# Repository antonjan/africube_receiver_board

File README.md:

This Repository has the Africube SDR Recever Boards V1.0<br>
Project is compleet but boards has not been build yet 3 Feb 2021
<br>

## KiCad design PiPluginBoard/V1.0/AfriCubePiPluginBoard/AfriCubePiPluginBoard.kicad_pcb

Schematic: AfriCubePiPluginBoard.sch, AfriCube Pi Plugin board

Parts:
BT1: Battery_Cell_3V; BatteryHolder_Keystone_3000_1x12mm
C1, C6, C7: 47uF; R_1210_3225Metric_Pad1.42x2.65mm_HandSolder
C2, C4, C11, C13, C14: 100nF; R_0805_2012Metric_Pad1.15x1.40mm_HandSolder
C3, C10, C12: 10uF; R_0805_2012Metric_Pad1.15x1.40mm_HandSolder
C5: 4.7uF; R_0805_2012Metric_Pad1.15x1.40mm_HandSolder
C9: 1uF; R_0805_2012Metric_Pad1.15x1.40mm_HandSolder
D1, D2: LED; R_0805_2012Metric_Pad1.15x1.40mm_HandSolder
D3, D4: BAV99; SOT-23
J1: USB_A; PinHeader_1x05_P1.00mm_Vertical
J2: SD_Card; microSD_HC_Hirose_DM3D-SF
J3: USB_B_Mini; USB_Mini-B_Lumberg_2486_01_Horizontal
J4: SODIMM-200; Conn_TE-DDR2-SODIMM-0.6-200P-doublesided
J7: Conn_01x04_Male; PinSocket_1x04_P2.54mm_Vertical
JP1: Jumper_Boot_Select; PinSocket_1x03_P2.54mm_Vertical
JP2: WDT_S0; SolderJumper-3_P1.3mm_Open_RoundedPad1.0x1.5mm
JP3: WDT_S1; SolderJumper-3_P1.3mm_Open_RoundedPad1.0x1.5mm
JP4: WDT_S2; SolderJumper-3_P1.3mm_Open_RoundedPad1.0x1.5mm
Q1, Q2, Q3: BSS138; SOT-23
R1, R3, R6: 47K; R_0805_2012Metric_Pad1.15x1.40mm_HandSolder
R2, R7: 470R; R_0805_2012Metric_Pad1.15x1.40mm_HandSolder
R4, R5, R8, R9, R10, R11, R14, R15, R16: 100K; R_0805_2012Metric_Pad1.15x1.40mm_HandSolder
R12, R13: 4K7; R_0805_2012Metric_Pad1.15x1.40mm_HandSolder
R17, R19: 270R; R_0805_2012Metric_Pad1.15x1.40mm_HandSolder
R18, R20: 150R; R_0805_2012Metric_Pad1.15x1.40mm_HandSolder
U1: FSUSB42MUX; MSOP-10_3x3mm_P0.5mm
U2: TLV70218_SOT23-5; SOT-23-5
U3: MAX6373; SOT-23-8
U4: DS3231M; SOIC-16W_7.5x10.3mm_P1.27mm

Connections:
+1V8: C3.1, J4.183, J4.184, J4.185, J4.186, R4.1, U2.5
+3V3: C4.1, C5.2, C7.2, C9.1, C14.1, D3.3, D4.3, J2.4, J4.39, J4.40, J4.41, J4.42, J4.191, J4.192, J4.193, J4.194, JP2.1, JP3.1, JP4.1, R1.2, R2.1, R7.1, R12.1, R13.1, R14.1, R15.1, R16.1, U1.1 (Vcc), U3.8, U4.2; also elsewhere on the board
+5V: C1.1, C6.1, J1.1, J4.197, J4.198, J4.199, R5.2, U2.1; also elsewhere on the board
+5V_USB: J3.1, JP1.1, Q3.1, R6.1; also elsewhere on the board
/Audio_L: J4.70, R17.2
/Audio_R: J4.84, R11.1, R19.2
/EMMC_DISABLE_N: J4.2, Q1.3
/EMMC_EN_N_1V8: J4.90, Q2.1, R4.2
/RTC_Int: J4.76, R15.2, U4.3
/RTC_Rst: J4.78, R16.2, U4.4
/USB_DM: J4.167, U1.4 (D-)
/USB_DP: J4.165, U1.3 (D+)
ANT_RELEASE: J4.81; also elsewhere on the board
BATT_OFF: J4.63; also elsewhere on the board
CHG_INH: J4.75; also elsewhere on the board
EPS_EOC: J4.57; also elsewhere on the board
EPS_SPI_CLK: J4.35; also elsewhere on the board
EPS_SPI_CS: J4.27; also elsewhere on the board
EPS_SPI_MISO: J4.29; also elsewhere on the board
EPS_SPI_MOSI: J4.33; also elsewhere on the board
GPIO4: J4.15; also elsewhere on the board
GPIO5: J4.17; also elsewhere on the board
GPIO6: J4.21; also elsewhere on the board
GPIO7: J4.23; also elsewhere on the board
GPIO12: J4.45; also elsewhere on the board
GPIO13: J4.47; also elsewhere on the board
GPIO14: J4.51; also elsewhere on the board
GPIO15: J4.53; also elsewhere on the board
GPIO17: J4.59; also elsewhere on the board
GPIO19: J4.65; also elsewhere on the board
GPIO21: J4.71; also elsewhere on the board
GPIO23: J4.77; also elsewhere on the board
GPIO25: J4.83; also elsewhere on the board
GPIO26: J4.87; also elsewhere on the board
GPIO27: J4.89; also elsewhere on the board
unnamed: BT1.1, U4.14
unnamed: C2.1, R5.1, U2.3
unnamed: C10.1, D3.1, D3.2, J7.1
unnamed: C10.2, C11.1, R17.1, R18.2
unnamed: C12.1, D4.1, D4.2, J7.3
unnamed: C12.2, C13.1, R19.1, R20.2
unnamed: D1.1, Q1.2, Q2.3
unnamed: D1.2, R2.2
unnamed: D2.2, R7.2
unnamed: J1.2, U1.8 (HSD2-)
unnamed: J1.3, U1.9 (HSD2+)
unnamed: J2.1, J4.24
unnamed: J2.2, J4.12
unnamed: J2.5, J4.10
unnamed: J2.7, J4.16
unnamed: J2.8, J4.18
unnamed: J2.9, J4.22
unnamed: J3.2, U1.6 (HSD1-)
unnamed: J3.3, U1.7 (HSD1+)
unnamed: J4.28, R9.1
unnamed: J4.30, R8.1
unnamed: J4.82, R10.1
unnamed: J4.177, U3.7
unnamed: JP1.2, Q1.1, R3.1
unnamed: JP2.2, U3.4
unnamed: JP3.2, U3.5
unnamed: JP4.2, U3.6
unnamed: Q3.3, R1.1, U1.2 (Sel)
unnamed: R14.2, U4.1
SCL1: J4.5, R12.2, U4.16; also elsewhere on the board
SCL2: J4.11; also elsewhere on the board
SDA1: J4.3, R13.2, U4.15; also elsewhere on the board
SDA2: J4.9; also elsewhere on the board
VBAT_SWITCH_EN: J4.69; also elsewhere on the board

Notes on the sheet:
GPIO0
GPIO1
GPIO2
GPIO3
GPIO4
GPIO5
GPIO6
GPIO7
GPIO8
GPIO9
GPIO10
GPIO11
GPIO0-27_VREF
GPIO28-45_VREF
GPIO12
GPIO13
GPIO14
GPIO15
GPIO16
GPIO17
GPIO18
GPIO19
GPIO20
GPIO21
GPIO22
GPIO23
GPIO24
GPIO25
GPIO26
GPIO27
DSIO_DN1
DSIO_DP1
DSIO_DN0
DSIO_DP0
DSIO_CN
DSIO_CP
USB_DP
USB_DM
RUN
VDD_CORE

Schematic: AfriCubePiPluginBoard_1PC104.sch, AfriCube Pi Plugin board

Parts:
C8: 10uF; R_0805_2012Metric_Pad1.15x1.40mm_HandSolder
J5: Barrel_Jack_MountingPin; BarrelJack_Wuerth_6941xx301002
P1: PC104

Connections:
+3V3: P1.47 (Pin47), P1.48 (Pin48); also elsewhere on the board
+5V: P1.51 (Pin51), P1.52 (Pin52); also elsewhere on the board
+5V_USB: P1.62 (Pin62); also elsewhere on the board
ANT_RELEASE: P1.44 (Pin44); also elsewhere on the board
BATT_OFF: P1.50 (Pin50); also elsewhere on the board
CHG_INH: P1.54 (Pin54); also elsewhere on the board
EPS_EOC: P1.11 (Pin11); also elsewhere on the board
EPS_SPI_CLK: P1.13 (Pin13); also elsewhere on the board
EPS_SPI_CS: P1.16 (Pin16); also elsewhere on the board
EPS_SPI_MISO: P1.14 (Pin14); also elsewhere on the board
EPS_SPI_MOSI: P1.15 (Pin15); also elsewhere on the board
SCL1: P1.85 (Pin85); also elsewhere on the board
SCL2: P1.65 (Pin65); also elsewhere on the board
SDA1: P1.81 (Pin81); also elsewhere on the board
SDA2: P1.58 (Pin58); also elsewhere on the board
VBAT_SWITCH_EN: P1.77 (Pin77); also elsewhere on the board
VCHARGE: C8.1, J5.1, P1.55 (Pin55), P1.56 (Pin56)

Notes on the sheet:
Kletskous PC104 connector
Umbilical DC plug (battery charging)

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
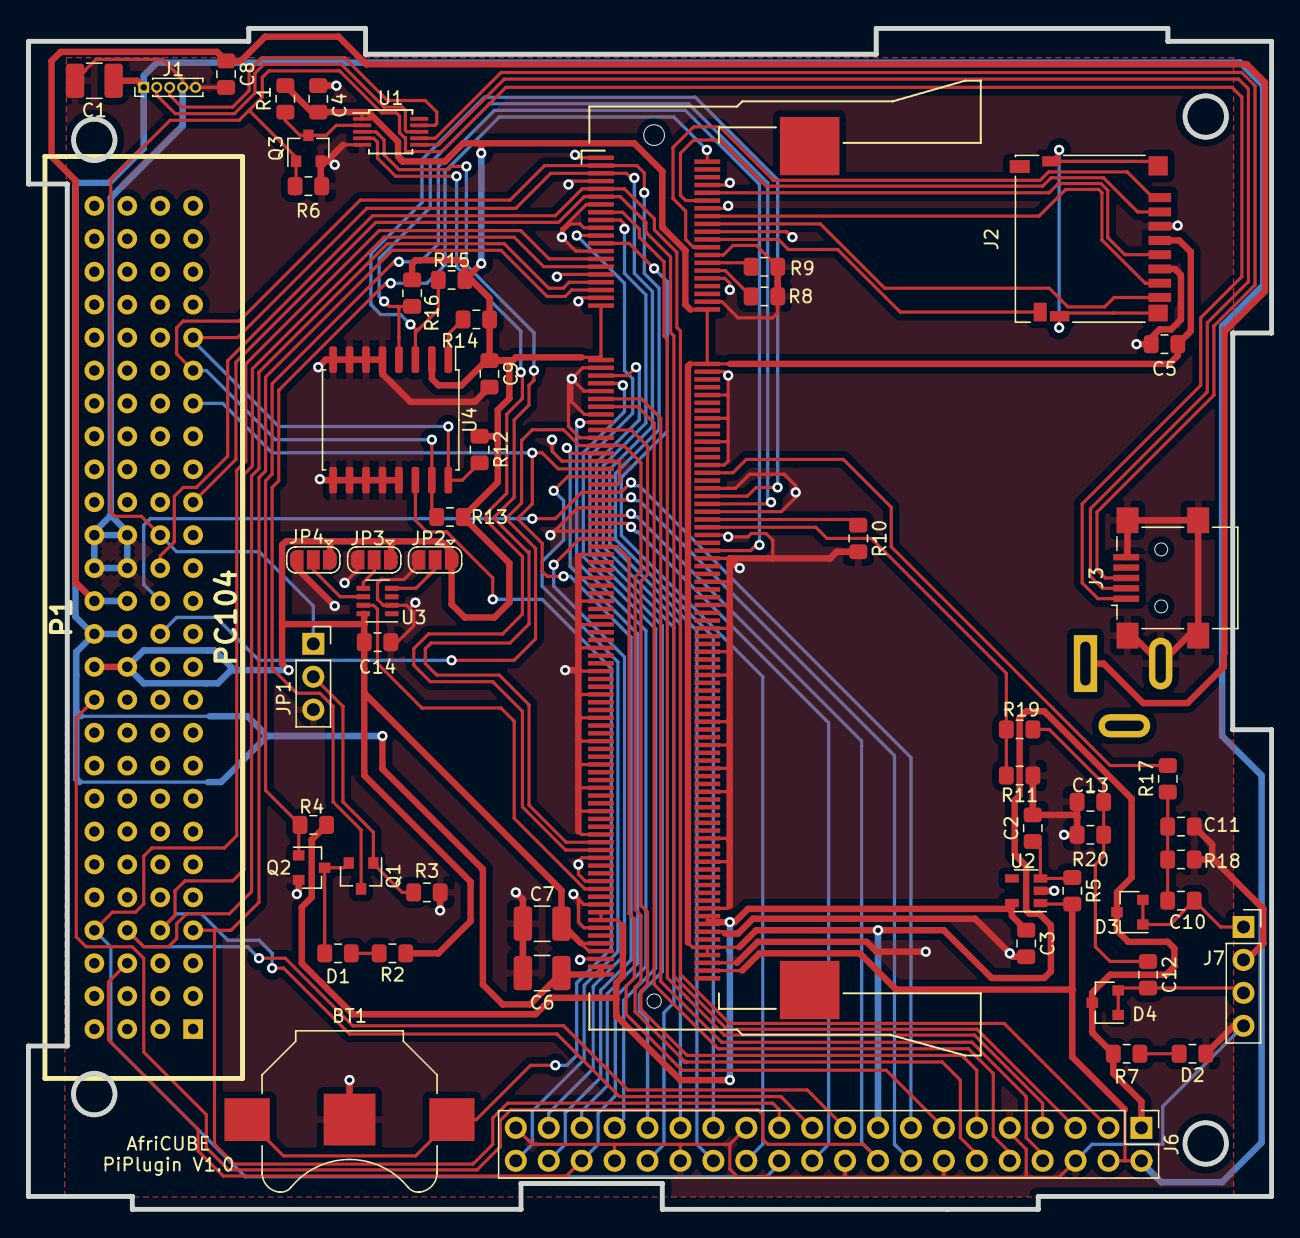
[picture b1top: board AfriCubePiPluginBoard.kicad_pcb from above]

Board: 2 copper layers, 95.9 x 91.1 mm, 58 parts (1 on the bottom side), 71 nets.

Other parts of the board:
J6: Raspberry_Pi_2_3; PinHeader_2x20_P2.54mm_Vertical

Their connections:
+3V3: J6.1, J6.17; also elsewhere on the board
+5V: J6.2, J6.4; also elsewhere on the board
ANT_RELEASE: J6.18; also elsewhere on the board
BATT_OFF: J6.12; also elsewhere on the board
CHG_INH: J6.15; also elsewhere on the board
EPS_EOC: J6.36; also elsewhere on the board
EPS_SPI_CLK: J6.23; also elsewhere on the board
EPS_SPI_CS: J6.24; also elsewhere on the board
EPS_SPI_MISO: J6.21; also elsewhere on the board
EPS_SPI_MOSI: J6.19; also elsewhere on the board
GPIO4: J6.7; also elsewhere on the board
GPIO5: J6.29; also elsewhere on the board
GPIO6: J6.31; also elsewhere on the board
GPIO7: J6.26; also elsewhere on the board
GPIO12: J6.32; also elsewhere on the board
GPIO13: J6.33; also elsewhere on the board
GPIO14: J6.8; also elsewhere on the board
GPIO15: J6.10; also elsewhere on the board
GPIO17: J6.11; also elsewhere on the board
GPIO19: J6.35; also elsewhere on the board
GPIO21: J6.40; also elsewhere on the board
GPIO23: J6.16; also elsewhere on the board
GPIO25: J6.22; also elsewhere on the board
GPIO26: J6.37; also elsewhere on the board
GPIO27: J6.13; also elsewhere on the board
SCL1: J6.28; also elsewhere on the board
SCL2: J6.5; also elsewhere on the board
SDA1: J6.27; also elsewhere on the board
SDA2: J6.3; also elsewhere on the board
VBAT_SWITCH_EN: J6.38; also elsewhere on the board

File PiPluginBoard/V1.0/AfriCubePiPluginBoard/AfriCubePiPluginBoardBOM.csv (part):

Source:,F:\AfriCube\PiPluginBoard\V1.0\AfriCubePiPluginBoard\AfriCubePiPluginBoard.sch,,,,,,,,,
Date:,2020/02/01 08:34,,,,,,,,,
Tool:,Eeschema (5.1.2)-2,,,,,,,,,
Generator:,C:\Program Files\KiCad\bin\scripting\plugins/bom_csv_grouped_by_value.py,,,,,,,,,
Component Count:,58,,,,,,,,,
,,,,,,,,,,
Individual Components:,,,,,,,,,,
,,,,,,,,,,
Item,Qty,Reference(s),Value,LibPart,Footprint,,,,,Datasheet
,,BT1,Battery_Cell_3V,Device:Battery_Cell,Battery:BatteryHolder_Keystone_3000_1x12mm,,,,,~
,,C1,47uF,Device:C,Resistor_SMD:R_1210_3225Metric_Pad1.42x2.65mm_HandSolder,,,,,~
,,C2,100nF,Device:C,Resistor_SMD:R_0805_2012Metric_Pad1.15x1.40mm_HandSolder,,,,,~
,,C3,10uF,Device:C,Resistor_SMD:R_0805_2012Metric_Pad1.15x1.40mm_HandSolder,,,,,~
,,C4,100nF,Device:C,Resistor_SMD:R_0805_2012Metric_Pad1.15x1.40mm_HandSolder,,,,,~
,,C5,4.7uF,Device:C,Resistor_SMD:R_0805_2012Metric_Pad1.15x1.40mm_HandSolder,,,,,~
,,C6,47uF,Device:C,Resistor_SMD:R_1210_3225Metric_Pad1.42x2.65mm_HandSolder,,,,,~
,,C7,47uF,Device:C,Resistor_SMD:R_1210_3225Metric_Pad1.42x2.65mm_HandSolder,,,,,~
,,C8,10uF,Device:C,Resistor_SMD:R_0805_2012Metric_Pad1.15x1.40mm_HandSolder,,,,,~
,,C9,1uF,Device:C,Resistor_SMD:R_0805_2012Metric_Pad1.15x1.40mm_HandSolder,,,,,~
,,C10,10uF,Device:C,Resistor_SMD:R_0805_2012Metric_Pad1.15x1.40mm_HandSolder,,,,,~
,,C11,100nF,Device:C,Resistor_SMD:R_0805_2012Metric_Pad1.15x1.40mm_HandSolder,,,,,~
,,C12,10uF,Device:C,Resistor_SMD:R_0805_2012Metric_Pad1.15x1.40mm_HandSolder,,,,,~
,,C13,100nF,Device:C,Resistor_SMD:R_0805_2012Metric_Pad1.15x1.40mm_HandSolder,,,,,~
,,C14,100nF,Device:C,Resistor_SMD:R_0805_2012Metric_Pad1.15x1.40mm_HandSolder,,,,,~
,,D1,LED,Device:LED,Resistor_SMD:R_0805_2012Metric_Pad1.15x1.40mm_HandSolder,,,,,~
,,D2,LED,Device:LED,Resistor_SMD:R_0805_2012Metric_Pad1.15x1.40mm_HandSolder,,,,,~
,,D3,BAV99,Diode:BAV99,Package_TO_SOT_SMD:SOT-23,,,,,https://assets.nexperia.com/documents/data-sheet/BAV99_SER.pdf
,,D4,BAV99,Diode:BAV99,Package_TO_SOT_SMD:SOT-23,,,,,https://assets.nexperia.com/documents/data-sheet/BAV99_SER.pdf
,,J1,USB_A,Connector:USB_A,Connector_PinHeader_1.00mm:PinHeader_1x05_P1.00mm_Vertical,,,,, ~
,,J2,SD_Card,Connector:SD_Card,Connector_Card:microSD_HC_Hirose_DM3D-SF,,,,,http://portal.fciconnect.com/Comergent//fci/drawing/10067847.pdf
,,J3,USB_B_Mini,Connector:USB_B_Mini,Connector_USB:USB_Mini-B_Lumberg_2486_01_Horizontal,,,,,~
,,J4,SODIMM-200,Connector:SODIMM-200,RaspberryPi:Conn_TE-DDR2-SODIMM-0.6-200P-doublesided,,,,,
,,J5,Barrel_Jack_MountingPin,Connector:Barrel_Jack_MountingPin,Connector_BarrelJack:BarrelJack_Wuerth_6941xx301002,,,,,~
,,J6,Raspberry_Pi_2_3,Connector:Raspberry_Pi_2_3,Connector_PinHeader_2.54mm:PinHeader_2x20_P2.54mm_Vertical,,,,,https://www.raspberrypi.org/documentation/hardware/raspberry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
,,J7,Conn_01x04_Male,Connector:Conn_01x04_Male,Connector_PinSocket_2.54mm:PinSocket_1x04_P2.54mm_Vertical,,,,,~
,,JP1,Jumper_Boot_Select,Jumper:Jumper_3_Open,Connector_PinSocket_2.54mm:PinSocket_1x03_P2.54mm_Vertical,,,,,~
,,JP2,WDT_S0,Jumper:SolderJumper_3_Open,Jumper:SolderJumper-3_P1.3mm_Open_RoundedPad1.0x1.5mm,,,,,~
,,JP3,WDT_S1,Jumper:SolderJumper_3_Open,Jumper:SolderJumper-3_P1.3mm_Open_RoundedPad1.0x1.5mm,,,,,~
,,JP4,WDT_S2,Jumper:SolderJumper_3_Open,Jumper:SolderJumper-3_P1.3mm_Open_RoundedPad1.0x1.5mm,,,,,~
,,P1,PC104,AfriCubePiPluginBoard-rescue:PC104-PC104,PC104B:PC104,,,,,
,,Q1,BSS138,Transistor_FET:BSS138,Package_TO_SOT_SMD:SOT-23,,,,,https://www.fairchildsemi.com/datasheets/BS/BSS138.pdf
,,Q2,BSS138,Transistor_FET:BSS138,Package_TO_SOT_SMD:SOT-23,,,,,https://www.fairchildsemi.com/datasheets/BS/BSS138.pdf
,,Q3,BSS138,Transistor_FET:BSS138,Package_TO_SOT_SMD:SOT-23,,,,,https://www.fairchildsemi.com/datasheets/BS/BSS138.pdf
,,R1,47K,Device:R,Resistor_SMD:R_0805_2012Metric_Pad1.15x1.40mm_HandSolder,,,,,~
,,R2,470R,Device:R,Resistor_SMD:R_0805_2012Metric_Pad1.15x1.40mm_HandSolder,,,,,~
,,R3,47K,Device:R,Resistor_SMD:R_0805_2012Metric_Pad1.15x1.40mm_HandSolder,,,,,~
,,R4,100K,Device:R,Resistor_SMD:R_0805_2012Metric_Pad1.15x1.40mm_HandSolder,,,,,~
,,R5,100K,Device:R,Resistor_SMD:R_0805_2012Metric_Pad1.15x1.40mm_HandSolder,,,,,~
,,R6,47K,Device:R,Resistor_SMD:R_0805_2012Metric_Pad1.15x1.40mm_HandSolder,,,,,~
,,R7,470R,Device:R,Resistor_SMD:R_0805_2012Metric_Pad1.15x1.40mm_HandSolder,,,,,~
,,R8,100K,Device:R,Resistor_SMD:R_0805_2012Metric_Pad1.15x1.40mm_HandSolder,,,,,~
,,R9,100K,Device:R,Resistor_SMD:R_0805_2012Metric_Pad1.15x1.40mm_HandSolder,,,,,~
,,R10,100K,Device:R,Resistor_SMD:R_0805_2012Metric_Pad1.15x1.40mm_HandSolder,,,,,~
,,R11,100K,Device:R,Resistor_SMD:R_0805_2012Metric_Pad1.15x1.40mm_HandSolder,,,,,~
,,R12,4K7,Device:R,Resistor_SMD:R_0805_2012Metric_Pad1.15x1.40mm_HandSolder,,,,,~
,,R13,4K7,Device:R,Resistor_SMD:R_0805_2012Metric_Pad1.15x1.40mm_HandSolder,,,,,~
,,R14,100K,Device:R,Resistor_SMD:R_0805_2012Metric_Pad1.15x1.40mm_HandSolder,,,,,~
,,R15,100K,Device:R,Resistor_SMD:R_0805_2012Metric_Pad1.15x1.40mm_HandSolder,,,,,~
,,R16,100K,Device:R,Resistor_SMD:R_0805_2012Metric_Pad1.15x1.40mm_HandSolder,,,,,~
,,R17,270R,Device:R,Resistor_SMD:R_0805_2012Metric_Pad1.15x1.40mm_HandSolder,,,,,~
,,R18,150R,Device:R,Resistor_SMD:R_0805_2012Metric_Pad1.15x1.40mm_HandSolder,,,,,~
,,R19,270R,Device:R,Resistor_SMD:R_0805_2012Metric_Pad1.15x1.40mm_HandSolder,,,,,~
,,R20,150R,Device:R,Resistor_SMD:R_0805_2012Metric_Pad1.15x1.40mm_HandSolder,,,,,~
,,U1,FSUSB42MUX,AfriCubePiPluginBoard-rescue:FSUSB42MUX-FSUSB42MUX,Package_SO:MSOP-10_3x3mm_P0.5mm,,,,,
,,U2,TLV70218_SOT23-5,Regulator_Linear:TLV70218_SOT23-5,Package_TO_SOT_SMD:SOT-23-5,,,,,http://www.ti.com/lit/ds/symlink/tlv702.pdf
,,U3,MAX6373,Power_Supervisor:MAX6373,Package_TO_SOT_SMD:SOT-23-8,,,,,https://datasheets.maximintegrated.com/en/ds/MAX6369-MAX6374.pdf
,,U4,DS3231M,Timer_RTC:DS3231M,Package_SO:SOIC-16W_7.5x10.3mm_P1.27mm,,,,,http://datasheets.maximintegrated.com/en/ds/DS3231.pdf
,,,,,,,,,,
,,,,,,,,,,
,,,,,,,,,,
Collated Components:,,,,,,,,,,
,,,,,,,,,,
Item,Qty,Reference(s),Value,LibPart,Footprint,Req,Have,Ordered from RS,RS part nr,Datasheet
1,1,BT1,Battery_Cell_3V,Device:Battery_Cell,Battery:BatteryHolder_Keystone_3000_1x12mm,3,0,5,219-7926,~
2,3,"C1, C6, C7",47uF (max 5V),Device:C,Resistor_SMD:R_1210_3225Metric_Pad1.42x2.65mm_HandSolder,9,1,10,788-3029/891-9817,~
3,5,"C2, C4, C11, C13, C14",100nF,Device:C,Resistor_SMD:R_0805_2012Metric_Pad1.15x1.40mm_HandSolder,15,25,0,264-4416,~
4,4,"C3, C8, C10, C12","10uF (1xmax13.5V, others max 3V3)",Device:C,Resistor_SMD:R_0805_2012Metric_Pad1.15x1.40mm_HandSolder,12,25+,0,723-6039,~
5,1,C5,4.7uF (max 3v3),Device:C,Resistor_SMD:R_0805_2012Metric_Pad1.15x1.40mm_HandSolder,3,0,10,152-6136,~
6,1,C9,1uF (max 3V),Device:C,Resistor_SMD:R_0805_2012Metric_Pad1.15x1.40mm_HandSolder,3,10,0,451-5770,~
7,2,"D1, D2",LED,Device:LED,Resistor_SMD:R_0805_2012Metric_Pad1.15x1.40mm_HandSolder,6,,,,~
8,2,"D3, D4",BAV99,Diode:BAV99,Package_TO_SOT_SMD:SOT-23,6,,,,https://assets.nexperia.com/documents/data-sheet/BAV99_SER.pdf
9,1,J1,USB_A,Connector:USB_A,Connector_PinHeader_1.00mm:PinHeader_1x05_P1.00mm_Vertical,3,,,, ~
10,1,J2,SD_Card,Connector:SD_Card,Connector_Card:microSD_HC_Hirose_DM3D-SF,3,,,,http://portal.fciconnect.com/Comergent//fci/drawing/10067847.pdf
11,1,J3,USB_B_Mini,Connector:USB_B_Mini,Connector_USB:USB_Mini-B_Lumberg_2486_01_Horizontal,3,,,,~
12,1,J4,SODIMM-200,Connector:SODIMM-200,RaspberryPi:Conn_TE-DDR2-SODIMM-0.6-200P-doublesided,3,,,,
13,1,J5,Barrel_Jack_MountingPin,Connector:Barrel_Jack_MountingPin,Connector_BarrelJack:BarrelJack_Wuerth_6941xx301002,3,0,5,,~
14,1,J6,Raspberry_Pi_2_3,Connector:Raspberry_Pi_2_3,Connector_PinHeader_2.54mm:PinHeader_2x20_P2.54mm_Vertical,3,0,,,https://www.raspberrypi.org/documentation/hardware/raspberry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
15,1,J7,Conn_01x04_Male,Connector:Conn_01x04_Male,Connector_PinSocket_2.54mm:PinSocket_1x04_P2.54mm_Vertical,3,many,0,,~
16,1,JP1,Jumper_Boot_Select,Jumper:Jumper_3_Open,Connector_PinSocket_2.54mm:PinSocket_1x03_P2.54mm_Vertical,3,many,0,,~
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
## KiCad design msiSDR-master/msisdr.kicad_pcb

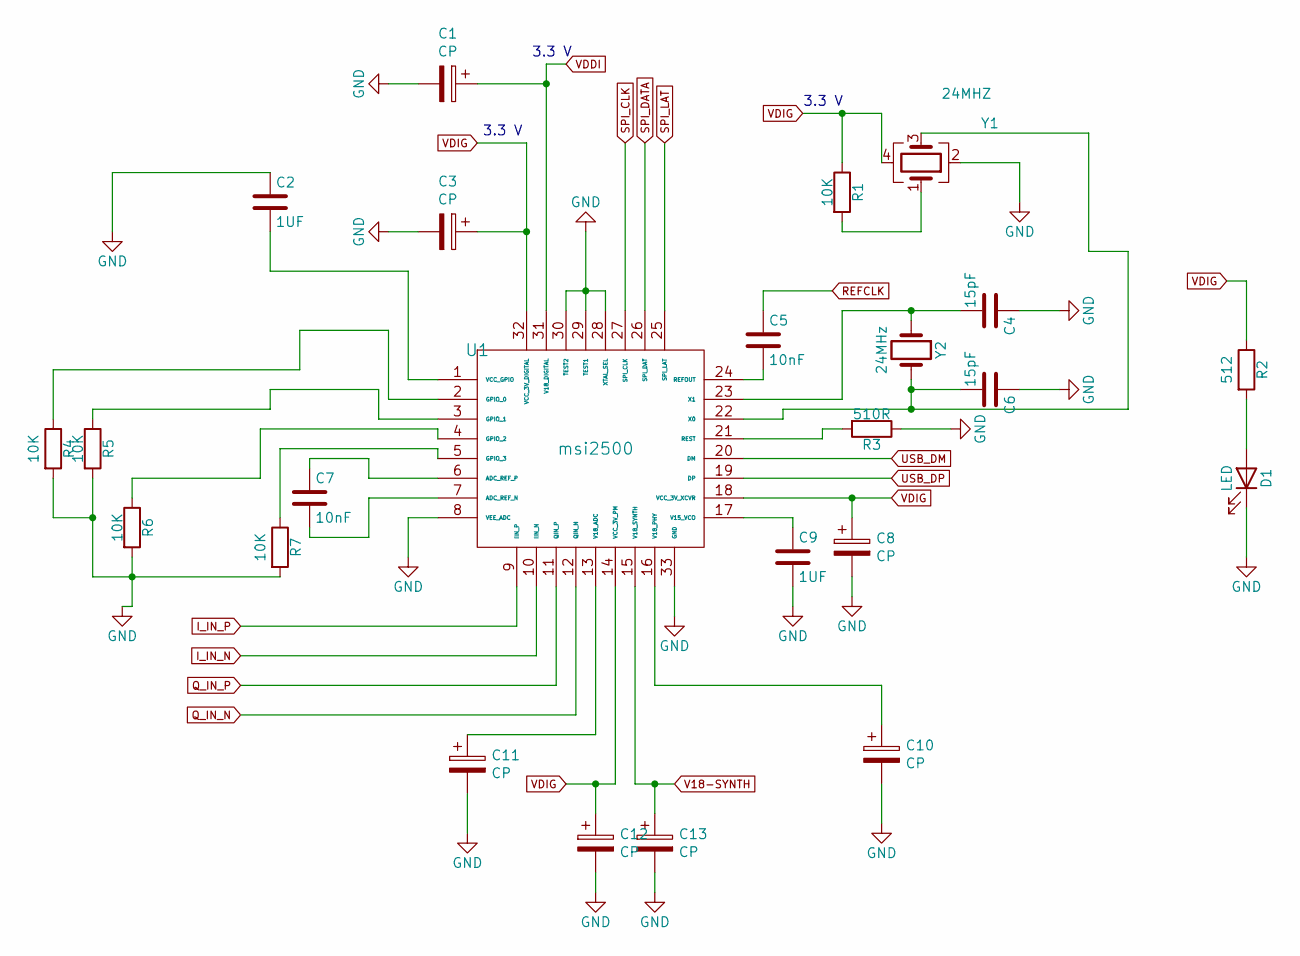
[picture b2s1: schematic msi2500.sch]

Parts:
C1, C3, C8, C10, C11, C12, C13: CP; CP_EIA-2012-12_Kemet-R
C2, C9: 1UF; C_0805_2012Metric
C4, C6: 15pF; C_0805_2012Metric
C5, C7: 10nF; C_0805_2012Metric
D1: LED; LED_0805_2012Metric
R1, R4, R5, R6, R7: 10K; R_0805_2012Metric
R2: 512; R_0805_2012Metric
R3: 510R; R_0805_2012Metric
U1: msi2500; QFN-32-1EP_5x5mm_P0.5mm_EP3.1x3.1mm
Y1: 24MHZ; Crystal_SMD_7050-4Pin_7.0x5.0mm
Y2: 24MHz; Crystal_SMD_HC49-SD

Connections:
GND: C1.2, C2.1, C3.2, C4.1, C6.1, C8.2, C9.2, C10.2, C11.2, C12.2, C13.2, D1.1 (K), R3.1, R4.2, R5.2, R6.2, R7.2, U1.8 (VEE_ADC), U1.28 (XTAL_SEL), U1.29 (TEST1), U1.30 (TEST2), U1.33 (GND), Y1.2; also elsewhere on the board
I_IN_N: U1.10 (IIN_N); also elsewhere on the board
I_IN_P: U1.9 (IIN_P); also elsewhere on the board
unnamed: C2.2, U1.1 (VCC_GPIO)
unnamed: C4.2, U1.23 (X1), Y2.1
unnamed: C5.2, U1.24 (REFOUT)
unnamed: C6.2, U1.22 (X0), Y1.3, Y2.2
unnamed: C7.1, U1.6 (ADC_REF_P)
unnamed: C7.2, U1.7 (ADC_REF_N)
unnamed: C9.1, U1.17 (V15_VCO)
unnamed: C10.1, U1.16 (V18_PHY)
unnamed: C11.1, U1.13 (V18_ADC)
unnamed: D1.2 (A), R2.2
unnamed: R1.2, Y1.1
unnamed: R3.2, U1.21 (REST)
unnamed: R4.1, U1.2 (GPIO_0)
unnamed: R5.1, U1.3 (GPIO_1)
unnamed: R6.1, U1.4 (GPIO_2)
unnamed: R7.1, U1.5 (GPIO_3)
Q_IN_N: U1.12 (QIN_N); also elsewhere on the board
Q_IN_P: U1.11 (QIN_P); also elsewhere on the board
REFCLK: C5.1; also elsewhere on the board
SPI_CLK: U1.27 (SPI_CLK); also elsewhere on the board
SPI_DATA: U1.26 (SPI_DAT); also elsewhere on the board
SPI_LAT: U1.25 (SPI_LAT); also elsewhere on the board
USB_DM: U1.20 (DM); also elsewhere on the board
USB_DP: U1.19 (DP); also elsewhere on the board
V18-SYNTH: C13.1, U1.15 (V18_SYNTH); also elsewhere on the board
VDDI: C1.1, U1.31 (V18_DIGITAL); also elsewhere on the board
VDIG: C3.1, C8.1, C12.1, R1.1, R2.1, U1.14 (VCC_3V_PM), U1.18 (VCC_3V_XCVR), U1.32 (VCC_3V_DIGITAL), Y1.4; also elsewhere on the board

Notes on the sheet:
3.3 V

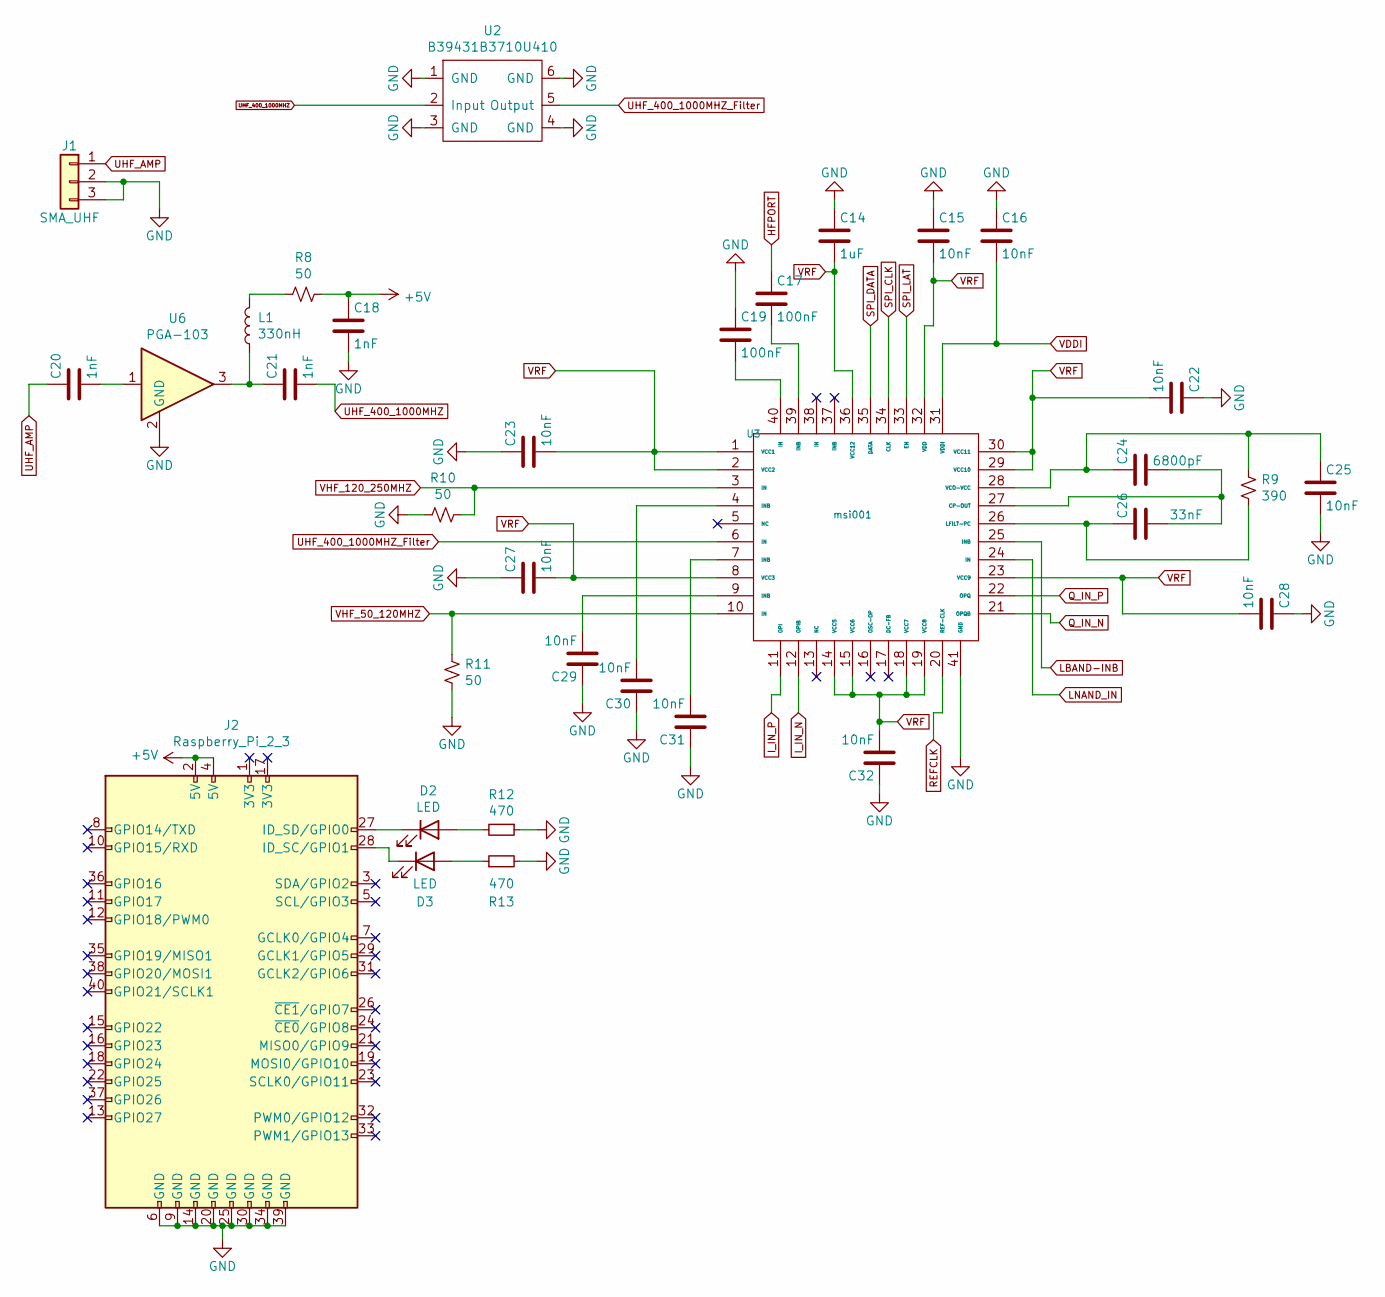
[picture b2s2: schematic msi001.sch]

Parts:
C14: 1uF; C_0805_2012Metric
C15, C16, C22, C23, C25, C27, C28, C29, C30, C31, C32: 10nF; C_0805_2012Metric
C17, C19: 100nF; C_0805_2012Metric
C18, C20, C21: 1nF; C_0805_2012Metric
C24: 6800pF; C_0805_2012Metric
C26: 33nF; C_0805_2012Metric
D2, D3: LED; LED_0805_2012Metric
J1: SMA_UHF; SMA_OPL_EMPTYHEAD
J2: Raspberry_Pi_2_3; PinHeader_2x20_P2.54mm_Vertical
L1: 330nH; L_0805_2012Metric
R8, R10, R11: 50; R_0805_2012Metric
R9: 390; R_0805_2012Metric
R12, R13: 470; R_0805_2012Metric
U2: B39431B3710U410; DFN-6-1EP_3x3mm_P1mm_EP1.5x2.4mm
U3: msi001; QFN-40-1EP_6x6mm_P0.5mm_EP4.6x4.6mm
U6: PGA-103; SOT-89-3

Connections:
GND: C14.1, C15.1, C16.1, C18.2, C19.1, C22.1, C23.1, C25.2, C27.1, C28.1, C29.1, C30.1, C31.1, C32.1, J1.2, J1.3, J2.6 (GND), J2.9 (GND), J2.14 (GND), J2.20 (GND), J2.25 (GND), J2.30 (GND), J2.34 (GND), J2.39 (GND), R10.2, R11.1, R12.1, R13.2, U2.1 (GND), U2.3 (GND), U2.4 (GND), U2.6 (GND), U3.41 (GND), U6.2 (GND); also elsewhere on the board
HFPORT: C17.1
I_IN_N: U3.12 (OPIB); also elsewhere on the board
I_IN_P: U3.11 (OPI); also elsewhere on the board
LBAND-INB: U3.25 (INB)
LNAND_IN: U3.24 (IN)
unnamed: C17.2, U3.39 (INB)
unnamed: C19.2, U3.40 (IN)
unnamed: C20.2, U6.1
unnamed: C21.1, L1.1, U6.3
unnamed: C24.1, C25.1, R9.1, U3.28 (VCO-VCC)
unnamed: C24.2, C26.2, U3.27 (CP-OUT)
unnamed: C26.1, R9.2, U3.26 (LFILT-PC)
unnamed: C29.2, U3.9 (INB)
unnamed: C30.2, U3.4 (INB)
unnamed: C31.2, U3.7 (INB)
unnamed: D2.1 (K), J2.27 (ID_SD/GPIO0)
unnamed: D2.2 (A), R12.2
unnamed: D3.1 (K), J2.28 (ID_SC/GPIO1)
unnamed: D3.2 (A), R13.1
unnamed: L1.2, R8.2
Q_IN_N: U3.21 (OPQB); also elsewhere on the board
Q_IN_P: U3.22 (OPQ); also elsewhere on the board
REFCLK: U3.20 (REF-CLK); also elsewhere on the board
SPI_CLK: U3.34 (CLK); also elsewhere on the board
SPI_DATA: U3.35 (DATA); also elsewhere on the board
SPI_LAT: U3.33 (EN); also elsewhere on the board
UHF_400_1000MHZ: C21.2, U2.2 (Input)
UHF_400_1000MHZ_Filter: U2.5 (Output), U3.6 (IN)
UHF_AMP: C20.1, J1.1
VDDI: C16.2, U3.31 (VDDI); also elsewhere on the board
VHF_50_120MHZ: R11.2, U3.10 (IN)
VHF_120_250MHZ: R10.1, U3.3 (IN)
VRF: C14.2, C15.2, C22.2, C23.2, C27.2, C28.2, C32.2, U3.1 (VCC1), U3.2 (VCC2), U3.8 (VCC3), U3.14 (VCC5), U3.15 (VCC6), U3.18 (VCC7), U3.19 (VCC8), U3.23 (VCC9), U3.29 (VCC10), U3.30 (VCC11), U3.32 (VDD), U3.36 (VCC12); also elsewhere on the board

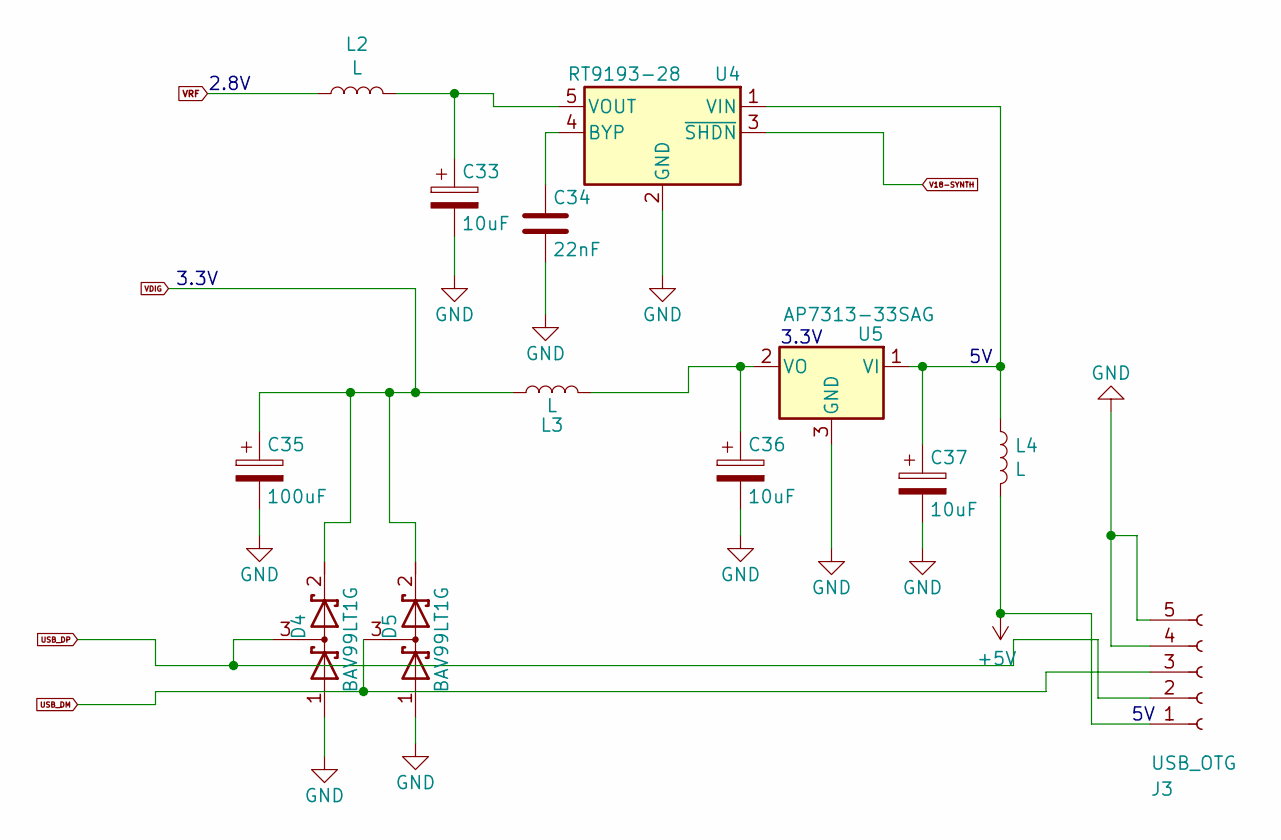
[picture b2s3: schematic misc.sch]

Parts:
C33, C36, C37: 10uF; CP_EIA-2012-12_Kemet-R
C34: 22nF; C_0805_2012Metric
C35: 100uF; CP_EIA-7343-15_Kemet-W
D4, D5: BAV99LT1G; SOT-23
J3: USB_OTG; PinHeader_1x05_P1.00mm_Vertical
L2, L3, L4: L; L_0805_2012Metric
U4: RT9193-28; SOT-23-5
U5: AP7313-33SAG; SOT-23

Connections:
GND: C33.2, C34.2, C35.2, C36.2, C37.2, D4.1 (A), D5.1 (A), J3.4, J3.5, U4.2 (GND), U5.3 (GND); also elsewhere on the board
unnamed: C33.1, L2.2, U4.5 (VOUT)
unnamed: C34.1, U4.4 (BYP)
unnamed: C36.1, L3.2, U5.2 (VO)
unnamed: C37.1, L4.1, U4.1 (VIN), U5.1 (VI)
USB_DM: D5.3 (common), J3.3; also elsewhere on the board
USB_DP: D4.3 (common), J3.2; also elsewhere on the board
V18-SYNTH: U4.3 (~SHDN~); also elsewhere on the board
VDIG: C35.1, D4.2 (K), D5.2 (K), L3.1; also elsewhere on the board
VRF: L2.1; also elsewhere on the board

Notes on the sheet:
3.3V
2.8V

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
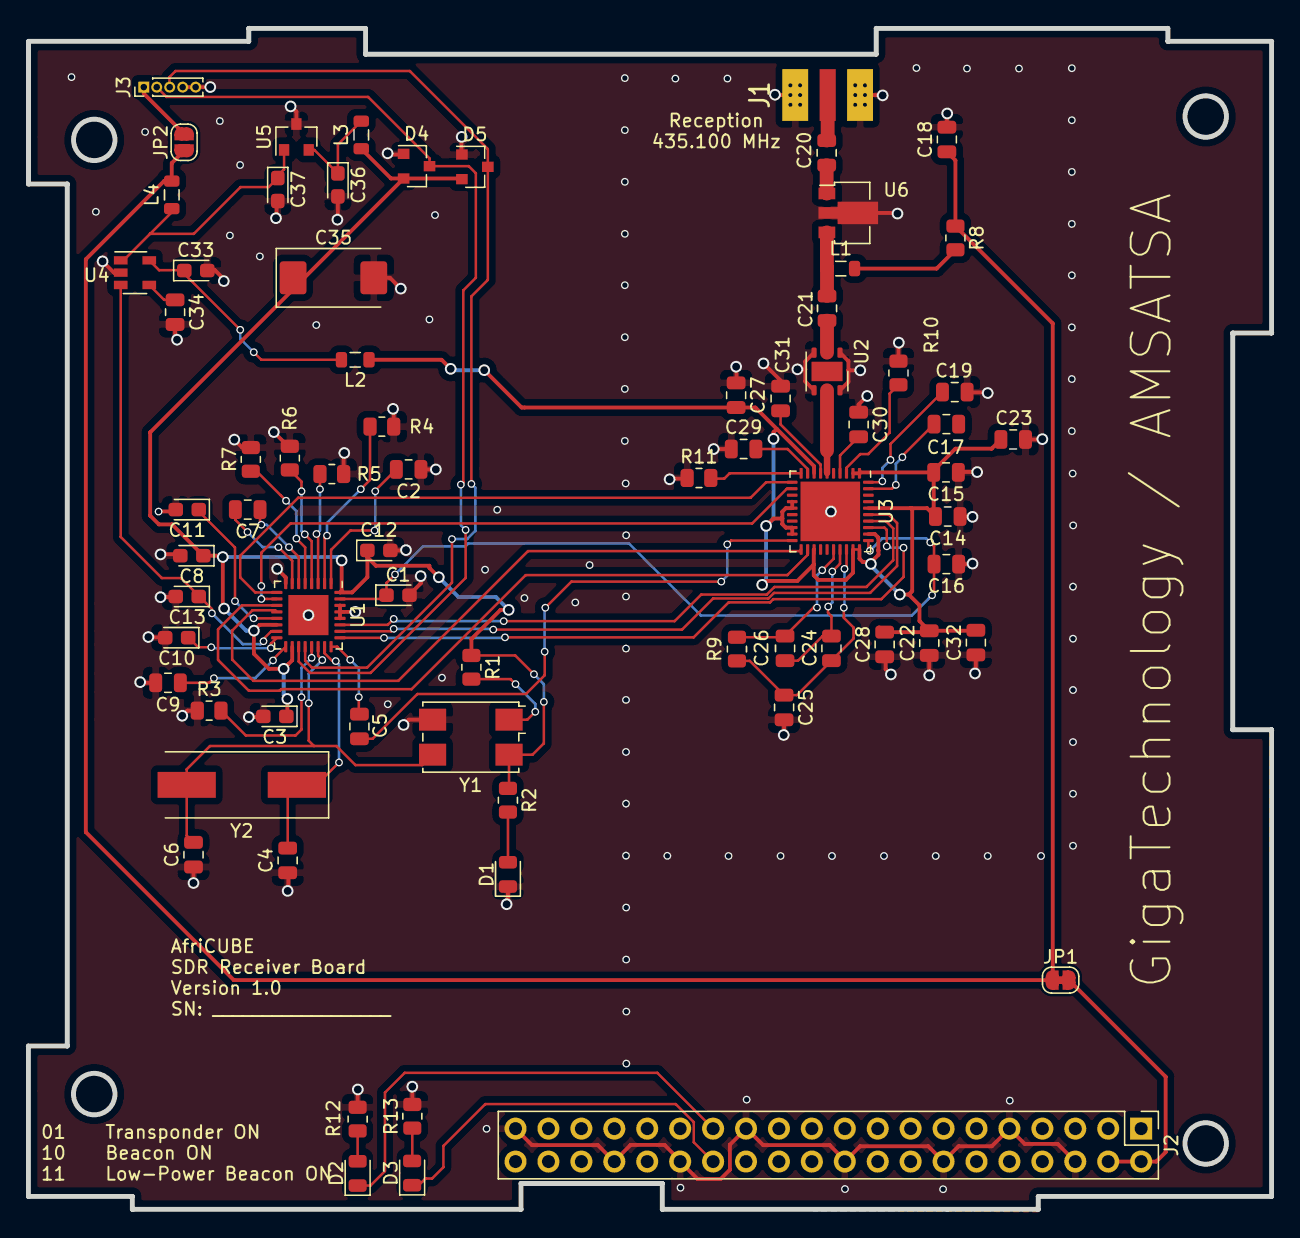
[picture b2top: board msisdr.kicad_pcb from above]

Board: 2 copper layers, 95.9 x 91.1 mm, 72 parts (0 on the bottom side), 58 nets.

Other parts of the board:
JP1: 5V Pi; SolderJumper-2_P1.3mm_Bridged_RoundedPad1.0x1.5mm
JP2: 5V USB; SolderJumper-2_P1.3mm_Open_RoundedPad1.0x1.5mm

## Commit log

2021-02-03 version 1.0_of RX board
2021-02-03 add picture
2021-02-03 adding board picture
2021-02-28 adding v2 2 filter front end filter
2021-02-28 Adding vertion nr
2022-05-18 adding second filter from shaun
